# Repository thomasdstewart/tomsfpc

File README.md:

# tomsfpc
Toms Front Panel Computer

It's a minimal Z80 computer. Heavily inspired by the Zeta256 (https://github.com/jmacarthur/zeta256/) Copyright Jim MacArthur.

This is currently work in progress

Eyrie link: https://eyrie.io/board/69ec80e52f42458caa95a5fe970ea00e

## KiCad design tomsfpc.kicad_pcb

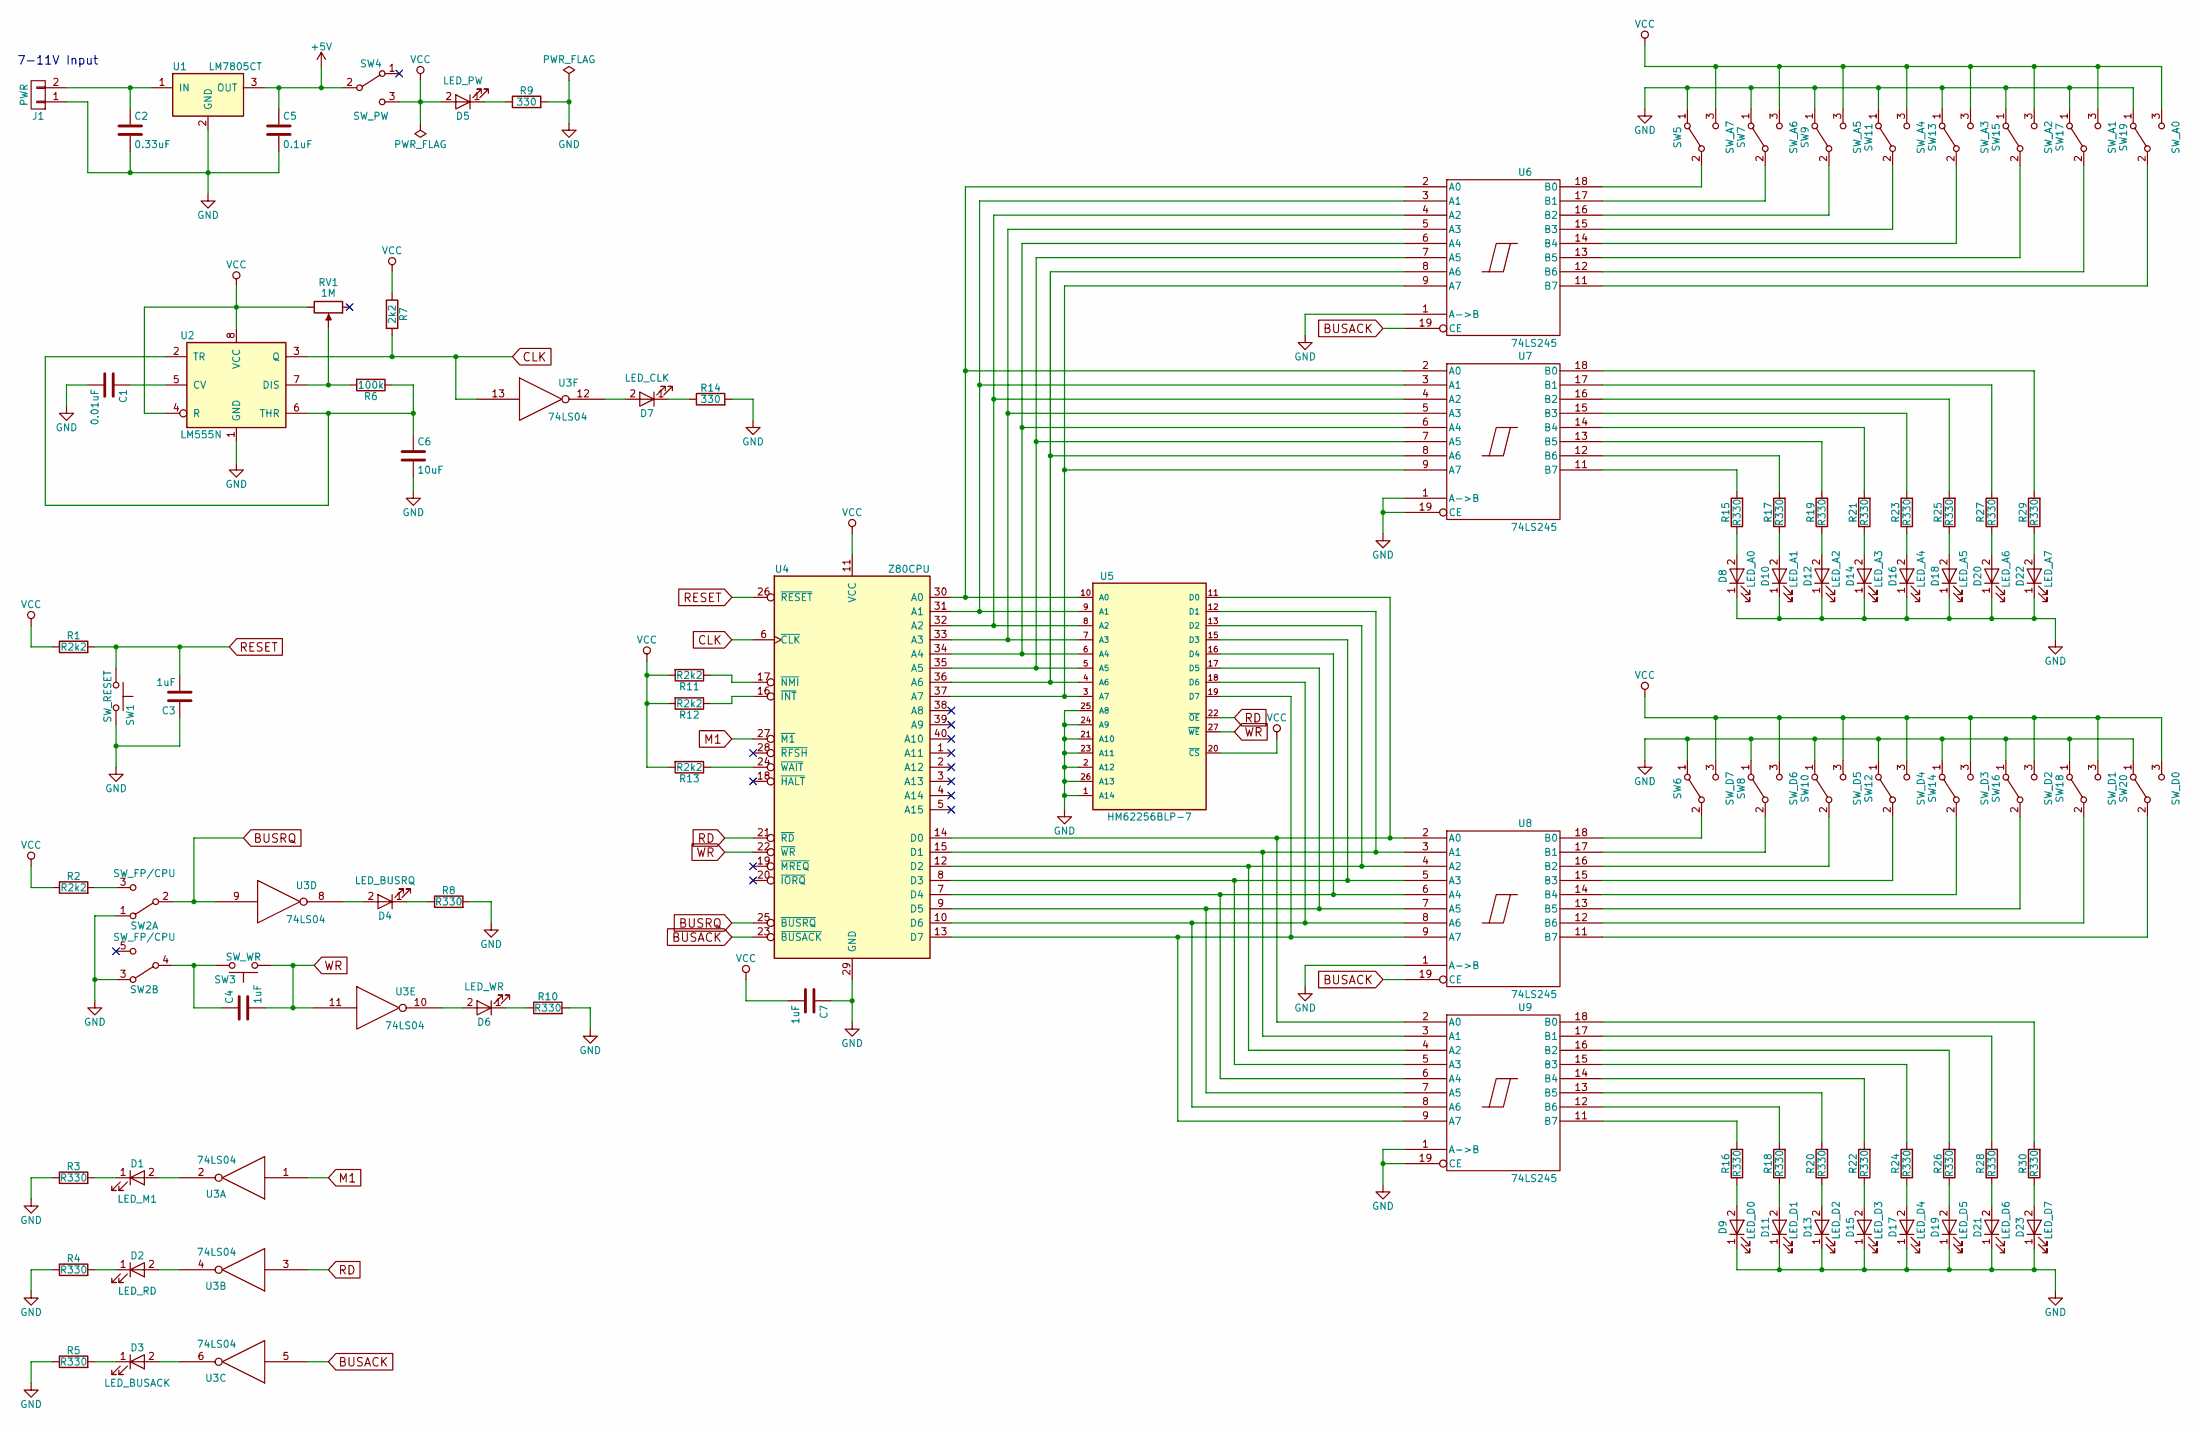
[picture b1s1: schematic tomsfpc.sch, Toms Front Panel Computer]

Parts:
C1: 0.01uF; C_Disc_D5.0mm_W2.5mm_P2.50mm
C2: 0.33uF; C_Disc_D5.0mm_W2.5mm_P2.50mm
C3, C4, C7: 1uF; C_Disc_D5.0mm_W2.5mm_P2.50mm
C5: 0.1uF; C_Disc_D5.0mm_W2.5mm_P2.50mm
C6: 10uF; C_Disc_D5.0mm_W2.5mm_P2.50mm
D1: LED_M1; LED_D3.0mm
D2: LED_RD; LED_D3.0mm
D3: LED_BUSACK; LED_D3.0mm
D4: LED_BUSRQ; LED_D3.0mm
D5: LED_PW; LED_D3.0mm
D6: LED_WR; LED_D3.0mm
D7: LED_CLK; LED_D3.0mm
D8: LED_A0; LED_D3.0mm
D9: LED_D0; LED_D3.0mm
D10: LED_A1; LED_D3.0mm
D11: LED_D1; LED_D3.0mm
D12: LED_A2; LED_D3.0mm
D13: LED_D2; LED_D3.0mm
D14: LED_A3; LED_D3.0mm
D15: LED_D3; LED_D3.0mm
D16: LED_A4; LED_D3.0mm
D17: LED_D4; LED_D3.0mm
D18: LED_A5; LED_D3.0mm
D19: LED_D5; LED_D3.0mm
D20: LED_A6; LED_D3.0mm
D21: LED_D6; LED_D3.0mm
D22: LED_A7; LED_D3.0mm
D23: LED_D7; LED_D3.0mm
J1: PWR; Pin_Header_Straight_1x02_Pitch2.00mm
R1, R2, R11, R12, R13: R2k2; R_Axial_DIN0411_L9.9mm_D3.6mm_P15.24mm_Horizontal
R3, R4, R5, R8, R10, R15, R16, R17, R18, R19, R20, R21, R22, R23, R24, R25, R26, R27, R28, R29, R30: R330; R_Axial_DIN0411_L9.9mm_D3.6mm_P15.24mm_Horizontal
R6: 100k; R_Axial_DIN0411_L9.9mm_D3.6mm_P15.24mm_Horizontal
R7: 2k2; R_Axial_DIN0411_L9.9mm_D3.6mm_P15.24mm_Horizontal
R9, R14: 330; R_Axial_DIN0411_L9.9mm_D3.6mm_P15.24mm_Horizontal
RV1: 1M; Potentiometer_WirePads
SW1: SW_RESET; SW_PUSH
SW2: SW_FP/CPU; SW_DPDT_EBAY
SW3: SW_WR; SW_PUSH
SW4: SW_PW; SW_Micro_SPST
SW5: SW_A7; SW_DPDT_EBAY_SPP
SW6: SW_D7; SW_DPDT_EBAY_SPP
SW7: SW_A6; SW_DPDT_EBAY_SPP
SW8: SW_D6; SW_DPDT_EBAY_SPP
SW9: SW_A5; SW_DPDT_EBAY_SPP
SW10: SW_D5; SW_DPDT_EBAY_SPP
SW11: SW_A4; SW_DPDT_EBAY_SPP
SW12: SW_D4; SW_DPDT_EBAY_SPP
SW13: SW_A3; SW_DPDT_EBAY_SPP
SW14: SW_D3; SW_DPDT_EBAY_SPP
SW15: SW_A2; SW_DPDT_EBAY_SPP
SW16: SW_D2; SW_DPDT_EBAY_SPP
SW17: SW_A1; SW_DPDT_EBAY_SPP
SW18: SW_D1; SW_DPDT_EBAY_SPP
SW19: SW_A0; SW_DPDT_EBAY_SPP
SW20: SW_D0; SW_DPDT_EBAY_SPP
U1: LM7805CT; TO-220_Vertical
U2: LM555N; DIP-8_W7.62mm_Socket
U3: 74LS04; DIP-14_W7.62mm_Socket
U4: Z80CPU; DIP-40_W15.24mm_Socket
U5: HM62256BLP-7; DIP-28_W15.24mm_Socket
U6, U7, U8, U9: 74LS245; DIP-20_W7.62mm_Socket

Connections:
+5V: C5.1, SW4.2 (B), U1.3 (OUT)
BUSACK: U3.5, U4.23 (~BUSACK~), U6.19 (CE), U8.19 (CE)
BUSRQ: SW2.2 (B), U3.9, U4.25 (~BUSRQ~)
CLK: R7.2, U2.3 (Q), U3.13, U4.6 (~CLK~)
M1: U3.1, U4.27 (~M1~)
unnamed: C1.1, U2.5 (CV)
unnamed: C2.1, J1.2, U1.1 (IN)
unnamed: C4.1, SW2.4 (B), SW3.2
unnamed: C6.1, R6.1, U2.2 (TR), U2.6 (THR)
unnamed: D1.1 (K), R3.2
unnamed: D1.2 (A), U3.2
unnamed: D2.1 (K), R4.2
unnamed: D2.2 (A), U3.4
unnamed: D3.1 (K), R5.2
unnamed: D3.2 (A), U3.6
unnamed: D4.1 (K), R8.1
unnamed: D4.2 (A), U3.8
unnamed: D5.1 (K), R9.1
unnamed: D6.1 (K), R10.1
unnamed: D6.2 (A), U3.10
unnamed: D7.1 (K), R14.1
unnamed: D7.2 (A), U3.12
unnamed: D8.2 (A), R15.1
unnamed: D9.2 (A), R16.1
unnamed: D10.2 (A), R17.1
unnamed: D11.2 (A), R18.1
unnamed: D12.2 (A), R19.1
unnamed: D13.2 (A), R20.1
unnamed: D14.2 (A), R21.1
unnamed: D15.2 (A), R22.1
unnamed: D16.2 (A), R23.1
unnamed: D17.2 (A), R24.1
unnamed: D18.2 (A), R25.1
unnamed: D19.2 (A), R26.1
unnamed: D20.2 (A), R27.1
unnamed: D21.2 (A), R28.1
unnamed: D22.2 (A), R29.1
unnamed: D23.2 (A), R30.1
unnamed: R6.2, RV1.2, U2.7 (DIS)
unnamed: R11.1, U4.17 (~NMI~)
unnamed: R12.1, U4.16 (~INT~)
unnamed: R13.1, U4.24 (~WAIT~)
unnamed: R15.2, U7.11 (B7)
unnamed: R16.2, U9.11 (B7)
unnamed: R17.2, U7.12 (B6)
unnamed: R18.2, U9.12 (B6)
unnamed: R19.2, U7.13 (B5)
unnamed: R20.2, U9.13 (B5)
unnamed: R21.2, U7.14 (B4)
unnamed: R22.2, U9.14 (B4)
unnamed: R23.2, U7.15 (B3)
unnamed: R24.2, U9.15 (B3)
unnamed: R25.2, U7.16 (B2)
unnamed: R26.2, U9.16 (B2)
unnamed: R27.2, U7.17 (B1)
unnamed: R28.2, U9.17 (B1)
unnamed: R29.2, U7.18 (B0)
unnamed: R30.2, U9.18 (B0)
unnamed: SW5.2 (B), U6.18 (B0)
unnamed: SW6.2 (B), U8.18 (B0)
unnamed: SW7.2 (B), U6.17 (B1)
unnamed: SW8.2 (B), U8.17 (B1)
unnamed: SW9.2 (B), U6.16 (B2)
unnamed: SW10.2 (B), U8.16 (B2)
unnamed: SW11.2 (B), U6.15 (B3)
unnamed: SW12.2 (B), U8.15 (B3)
unnamed: SW13.2 (B), U6.14 (B4)
unnamed: SW14.2 (B), U8.14 (B4)
unnamed: SW15.2 (B), U6.13 (B5)
unnamed: SW16.2 (B), U8.13 (B5)
unnamed: SW17.2 (B), U6.12 (B6)
unnamed: SW18.2 (B), U8.12 (B6)
unnamed: SW19.2 (B), U6.11 (B7)
unnamed: SW20.2 (B), U8.11 (B7)
unnamed: U4.7 (D4), U5.16 (D4), U8.6 (A4), U9.6 (A4)
unnamed: U4.8 (D3), U5.15 (D3), U8.5 (A3), U9.5 (A3)
unnamed: U4.9 (D5), U5.17 (D5), U8.7 (A5), U9.7 (A5)
unnamed: U4.10 (D6), U5.18 (D6), U8.8 (A6), U9.8 (A6)
unnamed: U4.12 (D2), U5.13 (D2), U8.4 (A2), U9.4 (A2)
unnamed: U4.13 (D7), U5.19 (D7), U8.9 (A7), U9.9 (A7)
unnamed: U4.14 (D0), U5.11 (D0), U8.2 (A0), U9.2 (A0)
unnamed: U4.15 (D1), U5.12 (D1), U8.3 (A1), U9.3 (A1)
unnamed: U4.30 (A0), U5.10 (A0), U6.2 (A0), U7.2 (A0)
unnamed: U4.31 (A1), U5.9 (A1), U6.3 (A1), U7.3 (A1)
unnamed: U4.32 (A2), U5.8 (A2), U6.4 (A2), U7.4 (A2)
unnamed: U4.33 (A3), U5.7 (A3), U6.5 (A3), U7.5 (A3)
unnamed: U4.34 (A4), U5.6 (A4), U6.6 (A4), U7.6 (A4)
unnamed: U4.35 (A5), U5.5 (A5), U6.7 (A5), U7.7 (A5)
unnamed: U4.36 (A6), U5.4 (A6), U6.8 (A6), U7.8 (A6)
unnamed: U4.37 (A7), U5.3 (A7), U6.9 (A7), U7.9 (A7)
RD: U3.3, U4.21 (~RD~), U5.22 (~OE)
RESET: C3.2, R1.2, SW1.1, U4.26 (~RESET~)
VCC: C7.2, D5.2 (A), R1.1, R2.1, R7.1, R11.2, R12.2, R13.2, RV1.3, SW4.3 (C), SW5.3 (C), SW6.3 (C), SW7.3 (C), SW8.3 (C), SW9.3 (C), SW10.3 (C), SW11.3 (C), SW12.3 (C), SW13.3 (C), SW14.3 (C), SW15.3 (C), SW16.3 (C), SW17.3 (C), SW18.3 (C), SW19.3 (C), SW20.3 (C), U2.4 (R), U2.8 (VCC), U3.14 (VCC), U4.11 (VCC), U5.20 (~CS), U5.28 (VCC), U6.20 (VCC), U7.20 (VCC), U8.20 (VCC), U9.20 (VCC)
WR: C4.2, SW3.1, U3.11, U4.22 (~WR~), U5.27 (~WE)

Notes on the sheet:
7-11V Input

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
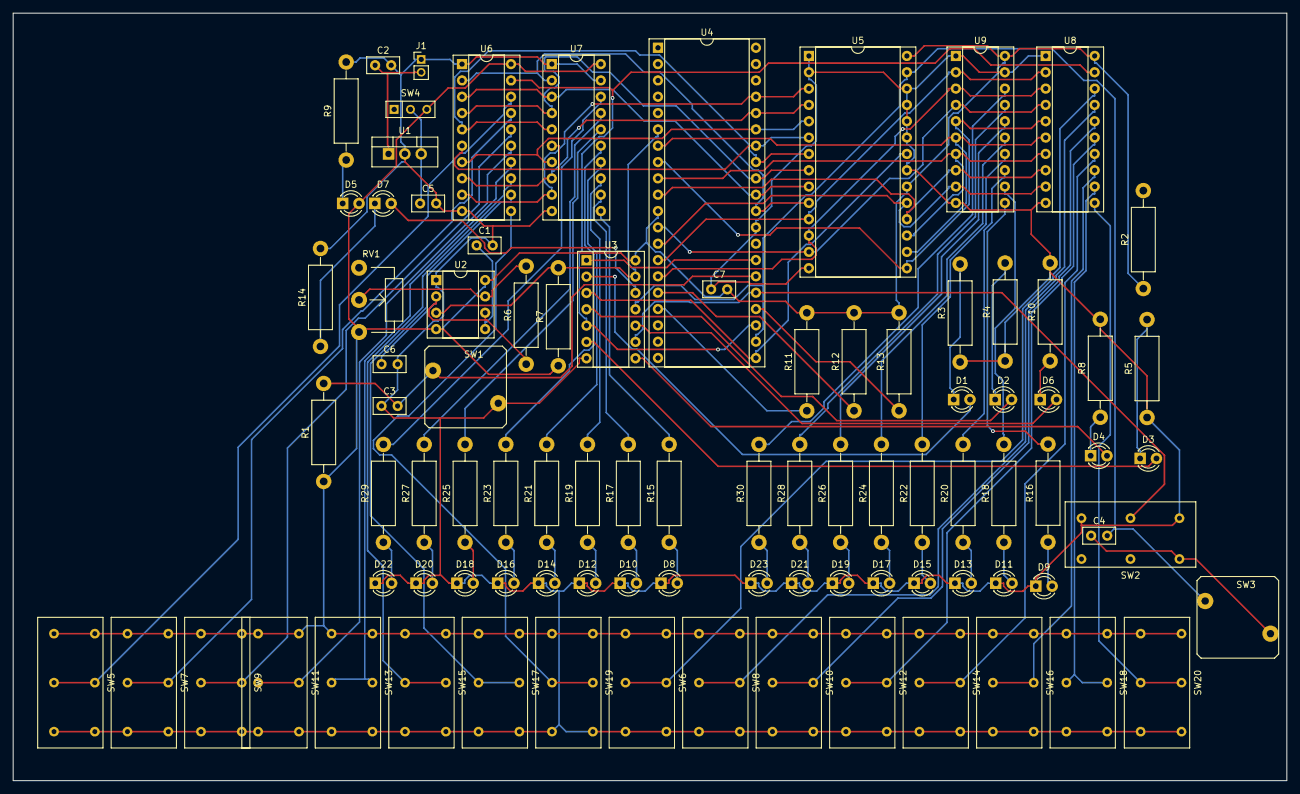
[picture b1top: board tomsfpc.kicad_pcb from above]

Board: 2 copper layers, 198.1 x 119.4 mm, 91 parts (0 on the bottom side), 95 nets.

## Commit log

2017-08-02 Initial commit of KiCad files
2017-08-02 README.md: add eyrie link
